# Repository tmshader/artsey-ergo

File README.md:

# Artsey Ergo
A 3D printable ergonomic wireless Artsey-based keyboard running ZMK.

## Features:
- NRF52840 chip for fast communication over BLE
- USB-C for charging, updating and communication instead of BLE
- Slightly modified Artsey 9.0.0 layout
- 128x32 OLED display for layers, battery status, time and other fun stuff
- Hotswappable choc v1 swiches
- Easily printable case

## Try or modify the project

Modify `ergogen/config.yaml` or use the provided config.

Run ergogen to create the base files:
```bash
ergogen ./ergogen -o .
```

This creates an `outlines` and a `pcbs` folder:
- The `pcbs` folder contains the starting point from which we can start routing and modifying the board.
- The `outlines` folder contains a bunch of mechanical drawings in `.dxf` format but the most important for us is `cad.dxf` which we can import into our favourite CAD software (Fusion, FreeCAD, Solidworks, etc.) and start designing a case for the keyboard.

## Upcoming changes
- Choc and MX compatible board versions
- Using the NRF52840 chip instead of a module
- Thread and Zigbee support (why not?)
- OTA Updates

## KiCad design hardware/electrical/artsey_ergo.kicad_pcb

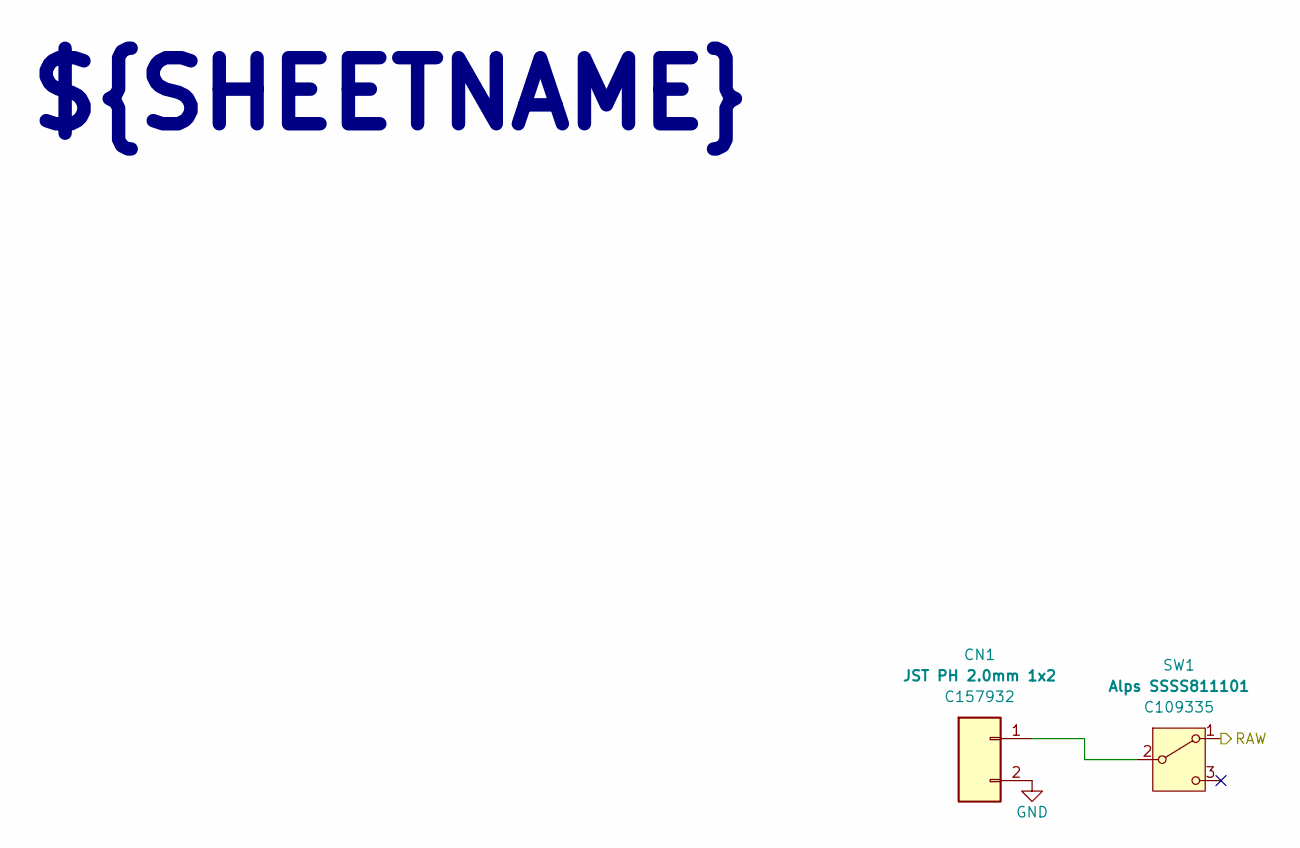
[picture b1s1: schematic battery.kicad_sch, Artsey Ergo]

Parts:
CN1: JST PH 2.0mm 1x2; battery_connector_jst_ph_2; LCSC C157932
SW1: Alps SSSS811101; power_switch_smd_side; LCSC C109335

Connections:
/Block Diagram/Battery/RAW: SW1.1 (A); also elsewhere on the board
GND: CN1.2; also elsewhere on the board
unnamed: CN1.1, SW1.2 (B)

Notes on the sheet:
${SHEETNAME}

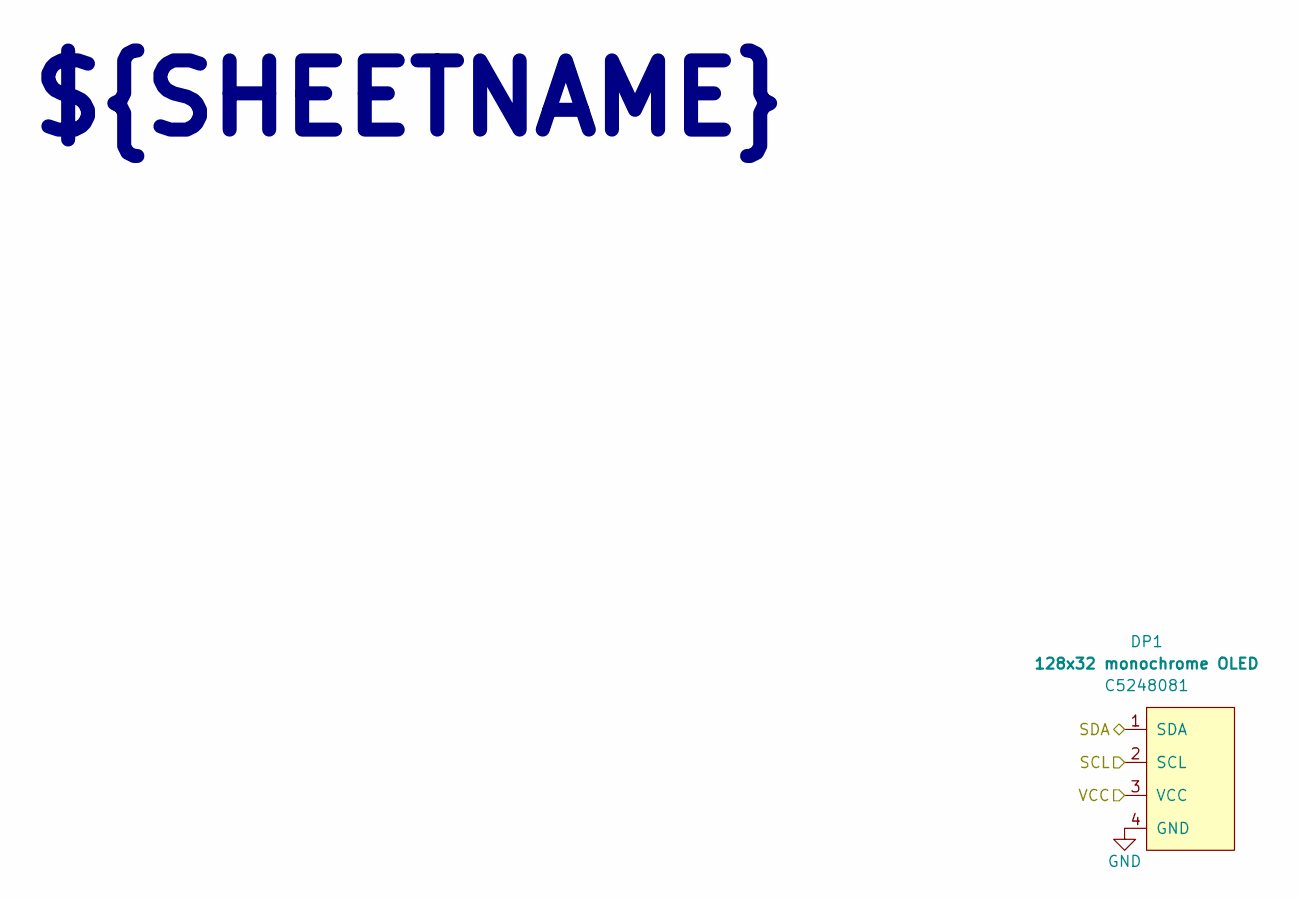
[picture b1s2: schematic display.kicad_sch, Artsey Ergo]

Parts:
DP1: 128x32 monochrome OLED; display_ssd1306; LCSC C5248081

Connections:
/Block Diagram/Display/SCL: DP1.2 (SCL); also elsewhere on the board
/Block Diagram/Display/SDA: DP1.1 (SDA); also elsewhere on the board
/Block Diagram/Display/VCC: DP1.3 (VCC); also elsewhere on the board
GND: DP1.4 (GND); also elsewhere on the board

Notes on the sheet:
${SHEETNAME}

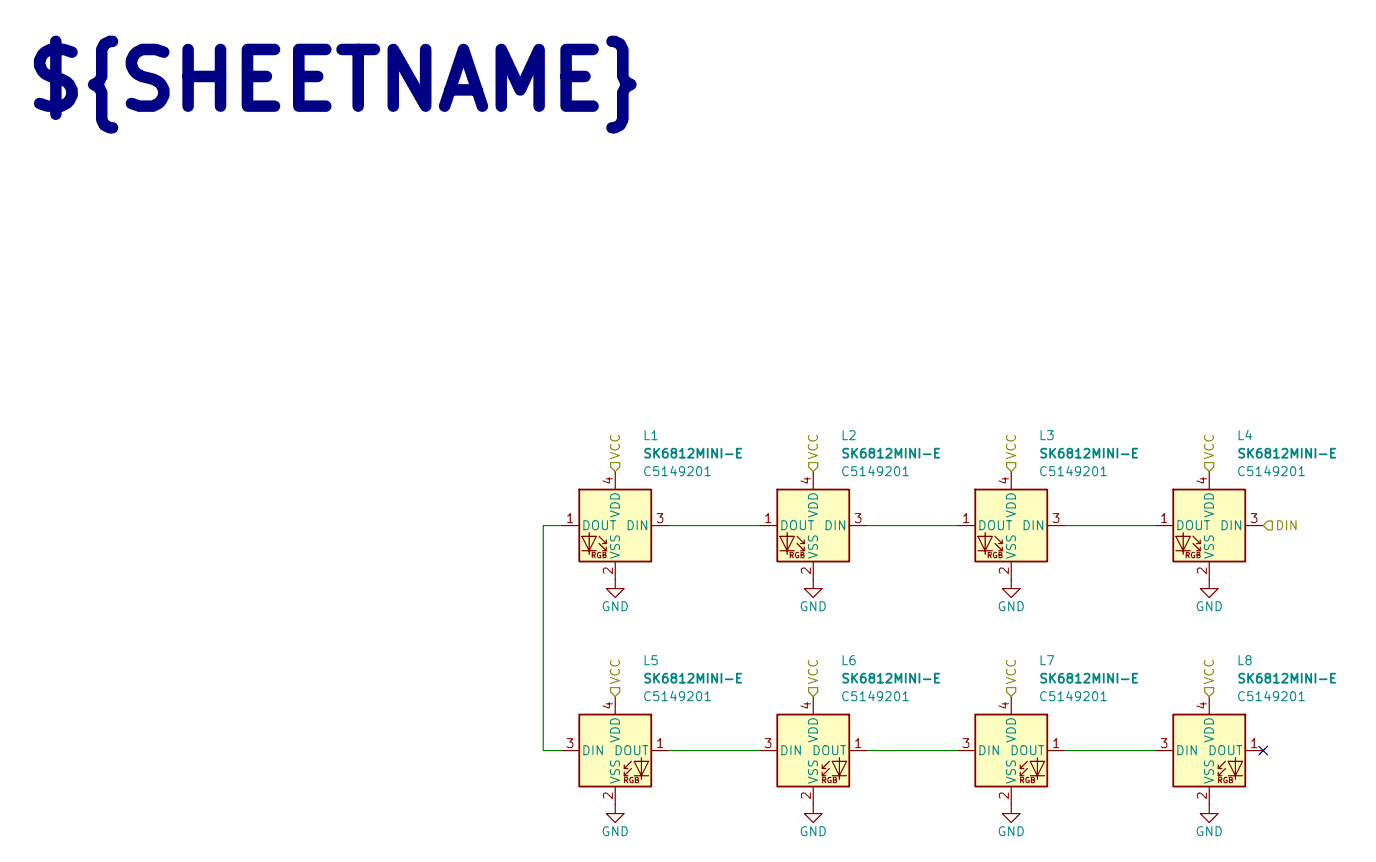
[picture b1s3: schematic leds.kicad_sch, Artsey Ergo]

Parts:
L1, L2, L3, L4, L5, L6, L7, L8: SK6812MINI-E; led_SK6812mini-e (per-key, reversible); LCSC C5149201

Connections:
/Block Diagram/Display/VCC: L1.4 (VDD), L2.4 (VDD), L3.4 (VDD), L4.4 (VDD), L5.4 (VDD), L6.4 (VDD), L7.4 (VDD), L8.4 (VDD); also elsewhere on the board
/Block Diagram/LEDs/DIN: L4.3 (DIN); also elsewhere on the board
GND: L1.2 (VSS), L2.2 (VSS), L3.2 (VSS), L4.2 (VSS), L5.2 (VSS), L6.2 (VSS), L7.2 (VSS), L8.2 (VSS); also elsewhere on the board
unnamed: L1.3 (DIN), L2.1 (DOUT)
unnamed: L1.1 (DOUT), L5.3 (DIN)
unnamed: L2.3 (DIN), L3.1 (DOUT)
unnamed: L3.3 (DIN), L4.1 (DOUT)
unnamed: L5.1 (DOUT), L6.3 (DIN)
unnamed: L6.1 (DOUT), L7.3 (DIN)
unnamed: L7.1 (DOUT), L8.3 (DIN)

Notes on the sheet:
${SHEETNAME}

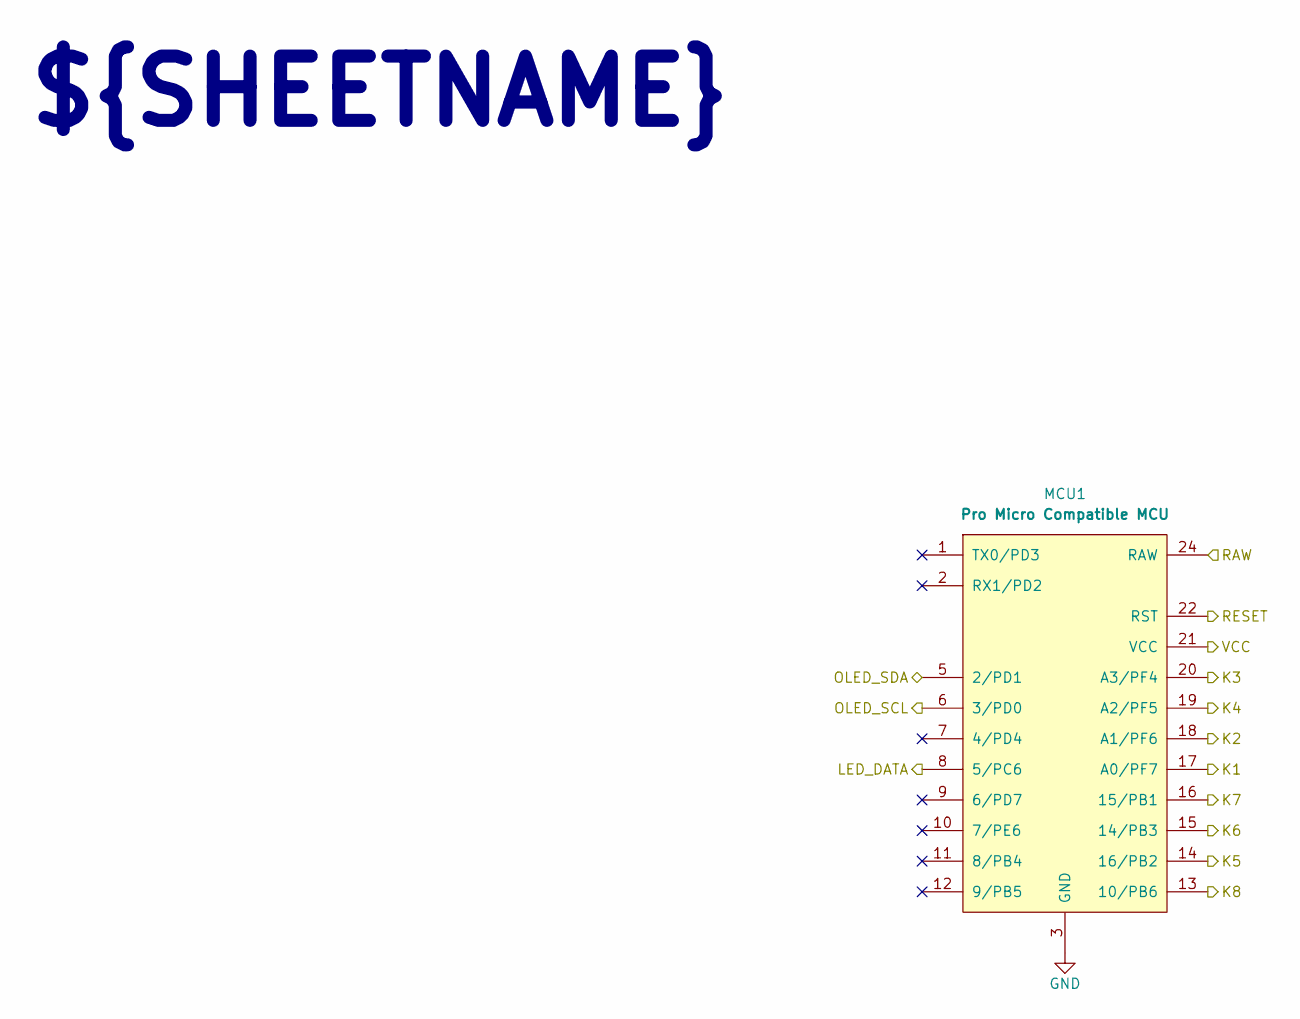
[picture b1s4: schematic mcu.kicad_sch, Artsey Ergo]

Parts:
MCU1: Pro Micro Compatible MCU; mcu_nice_nano

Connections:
/Block Diagram/Battery/RAW: MCU1.24 (RAW); also elsewhere on the board
/Block Diagram/Display/SCL: MCU1.6 (3/PD0); also elsewhere on the board
/Block Diagram/Display/SDA: MCU1.5 (2/PD1); also elsewhere on the board
/Block Diagram/Display/VCC: MCU1.21 (VCC); also elsewhere on the board
/Block Diagram/LEDs/DIN: MCU1.8 (5/PC6); also elsewhere on the board
/Block Diagram/MCU/K1: MCU1.17 (A0/PF7); also elsewhere on the board
/Block Diagram/MCU/K2: MCU1.18 (A1/PF6); also elsewhere on the board
/Block Diagram/MCU/K3: MCU1.20 (A3/PF4); also elsewhere on the board
/Block Diagram/MCU/K4: MCU1.19 (A2/PF5); also elsewhere on the board
/Block Diagram/MCU/K5: MCU1.14 (16/PB2); also elsewhere on the board
/Block Diagram/MCU/K6: MCU1.15 (14/PB3); also elsewhere on the board
/Block Diagram/MCU/K7: MCU1.16 (15/PB1); also elsewhere on the board
/Block Diagram/MCU/K8: MCU1.13 (10/PB6); also elsewhere on the board
/Block Diagram/MCU/RESET: MCU1.22 (RST); also elsewhere on the board
GND: MCU1.3 (GND), MCU1.4 (GND), MCU1.23 (GND); also elsewhere on the board

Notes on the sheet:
${SHEETNAME}

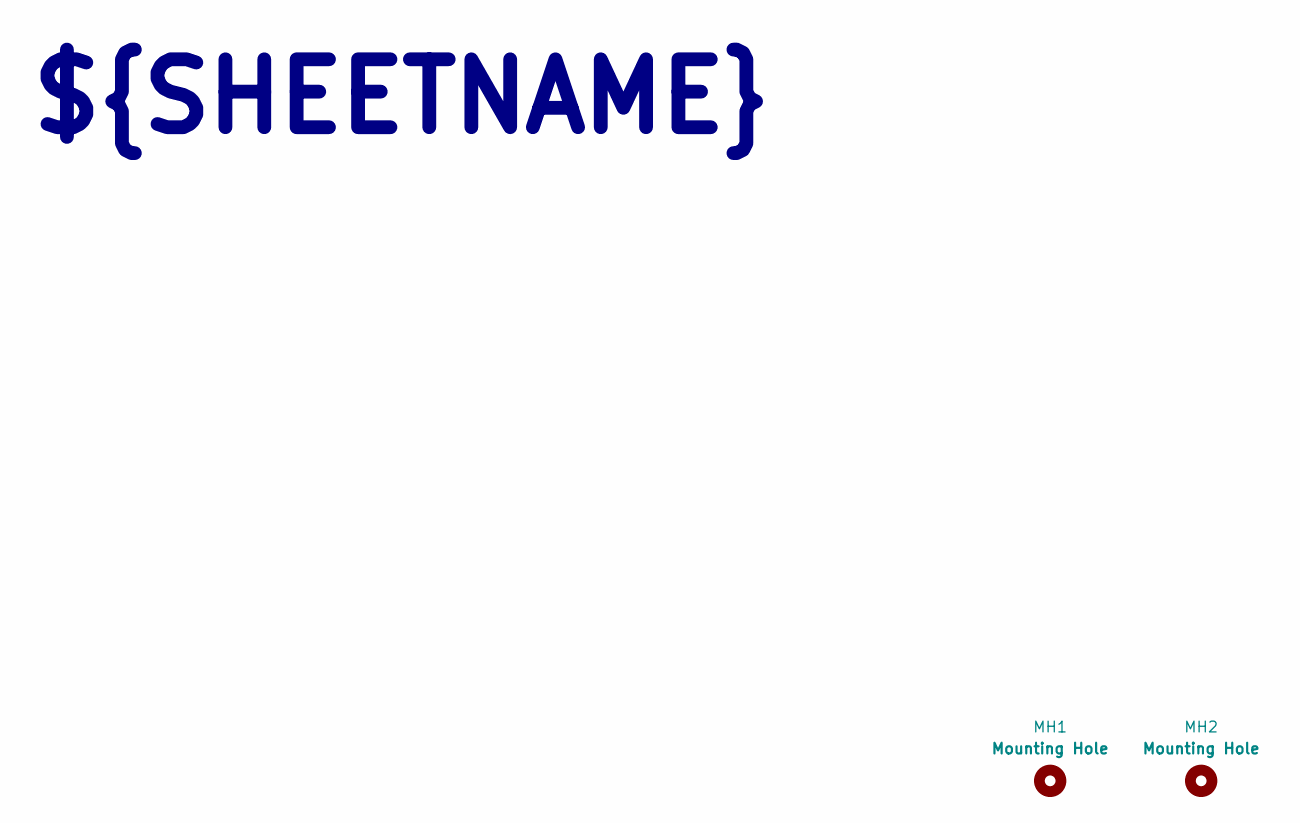
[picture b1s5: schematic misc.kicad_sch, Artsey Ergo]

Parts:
MH1, MH2: Mounting Hole; mounting_hole

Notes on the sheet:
${SHEETNAME}

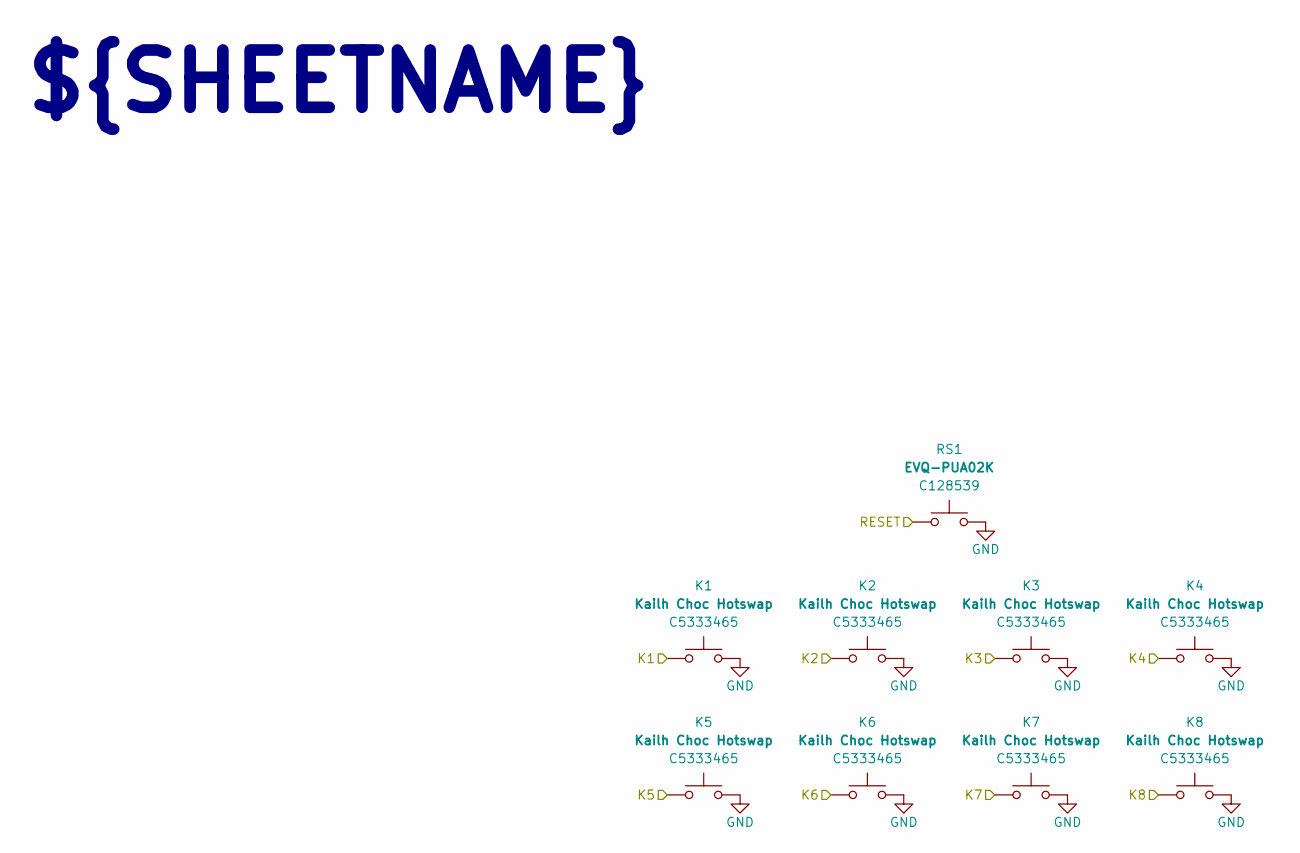
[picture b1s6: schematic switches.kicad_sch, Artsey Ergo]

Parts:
K1, K2, K3, K4, K5, K6, K7, K8: Kailh Choc Hotswap; switch_choc_v1_v2; LCSC C5333465
RS1: EVQ-PUA02K; reset_switch_smd_side; LCSC C128539

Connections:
/Block Diagram/MCU/K1: K1.1; also elsewhere on the board
/Block Diagram/MCU/K2: K2.1; also elsewhere on the board
/Block Diagram/MCU/K3: K3.1; also elsewhere on the board
/Block Diagram/MCU/K4: K4.1; also elsewhere on the board
/Block Diagram/MCU/K5: K5.1; also elsewhere on the board
/Block Diagram/MCU/K6: K6.1; also elsewhere on the board
/Block Diagram/MCU/K7: K7.1; also elsewhere on the board
/Block Diagram/MCU/K8: K8.1; also elsewhere on the board
/Block Diagram/MCU/RESET: RS1.1; also elsewhere on the board
GND: K1.2, K2.2, K3.2, K4.2, K5.2, K6.2, K7.2, K8.2, RS1.2; also elsewhere on the board

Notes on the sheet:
${SHEETNAME}

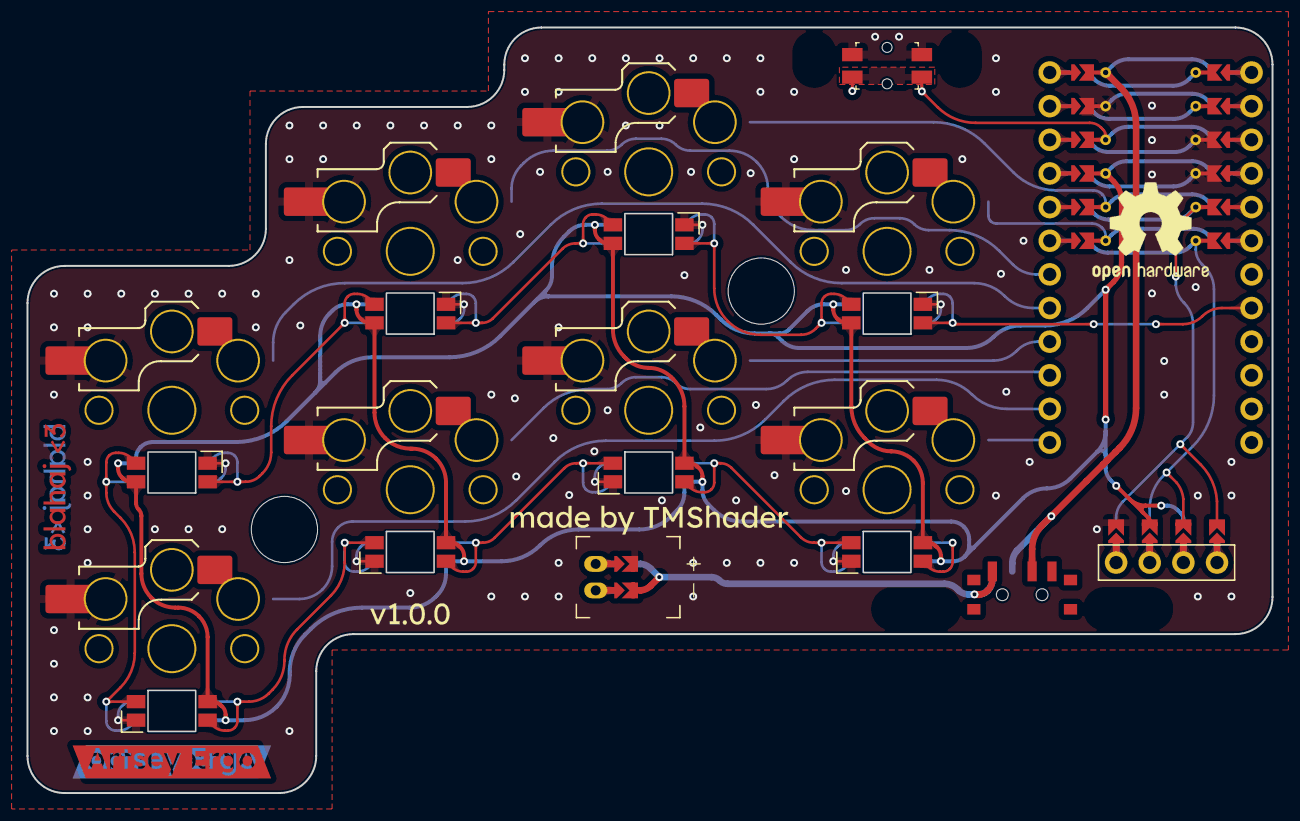
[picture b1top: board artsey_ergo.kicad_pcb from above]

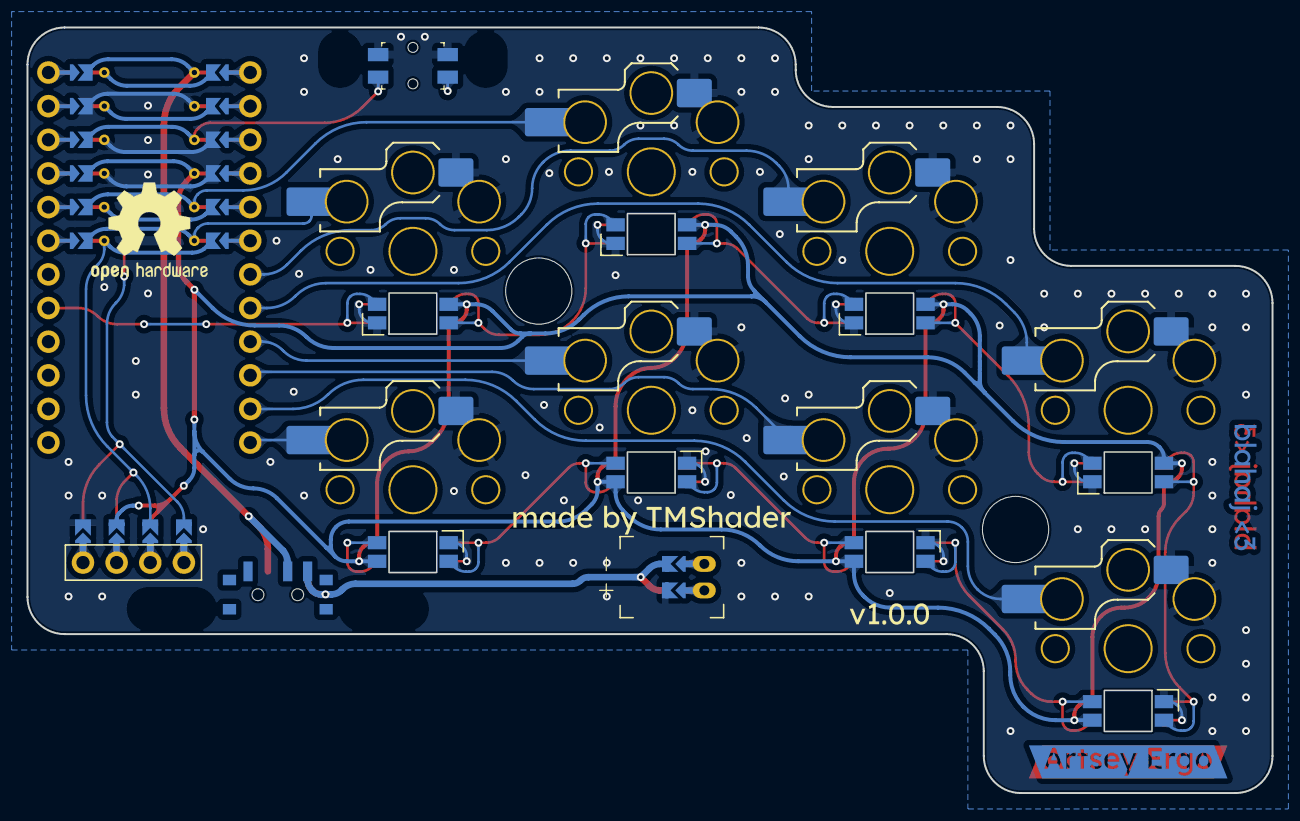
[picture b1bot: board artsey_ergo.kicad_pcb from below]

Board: 2 copper layers, 94.0 x 57.8 mm, 24 parts (19 on the bottom side), 23 nets.

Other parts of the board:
OL1: Value; Outline

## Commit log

2024-11-21 Add Image
2024-11-21 Update case image and add STL file, fix configuration errors
2024-11-22 Update cover
2024-11-25 Fix dimensions and heavily modify layout, generation process and case style
2024-11-26 Finish v1 PCB, clean up repo structure, tidy up ergogen config files, add LICENSE, add CAD and 3D models
2024-11-26 Fix clearance issues with battery connector and ground fill
2024-11-26 Fix DRC errors with battery connector
2024-11-27 Move LED data and I2C pins to high speed pin to avoid RF interference
2024-11-27 Add first firmware version and automated builds
2024-11-28 Add split keyboard mode
2024-12-05 Clean up and modify PCB, create Schematic, prepare for documentation generation
2024-12-05 Setup KiBot and GitHub Pages deploy
2024-12-05 Fix badges and CI-less deploy
2024-12-05 Include TARDIS script in page head
2024-12-06 Add panelized JLCPCB build, make actions faster by skipping rendering with a variable
2024-12-06 Update index page to include panelized builds
2024-12-06 Fix index page typo
2024-12-06 Fix actions problems
2024-12-06 Fix small errors in schematic and pcb
2024-12-10 Remove schematic renaming
2024-12-13 Fix actions bug
2024-12-13 Fix index.md typos and enable running actions on more conditions
2024-12-13 Fix table width problems and actions bug
2024-12-13 Small index.md fixes
2025-01-02 Fix pins and LEDs
2025-01-02 Fix pinout
2025-01-02 Fix underglow options
2025-01-02 Fix LED
2025-01-02 Revert LED config
2025-01-10 LED config testing
2025-01-10 Fix pin order
2025-01-10 RGB bindings
2025-01-11 Move RGB commands
2025-01-11 Display tweaks
2025-01-11 Disable unused split builds
2025-01-11 Disable display blanking and fix RGB layer
2025-01-11 Tweak RGB layer
